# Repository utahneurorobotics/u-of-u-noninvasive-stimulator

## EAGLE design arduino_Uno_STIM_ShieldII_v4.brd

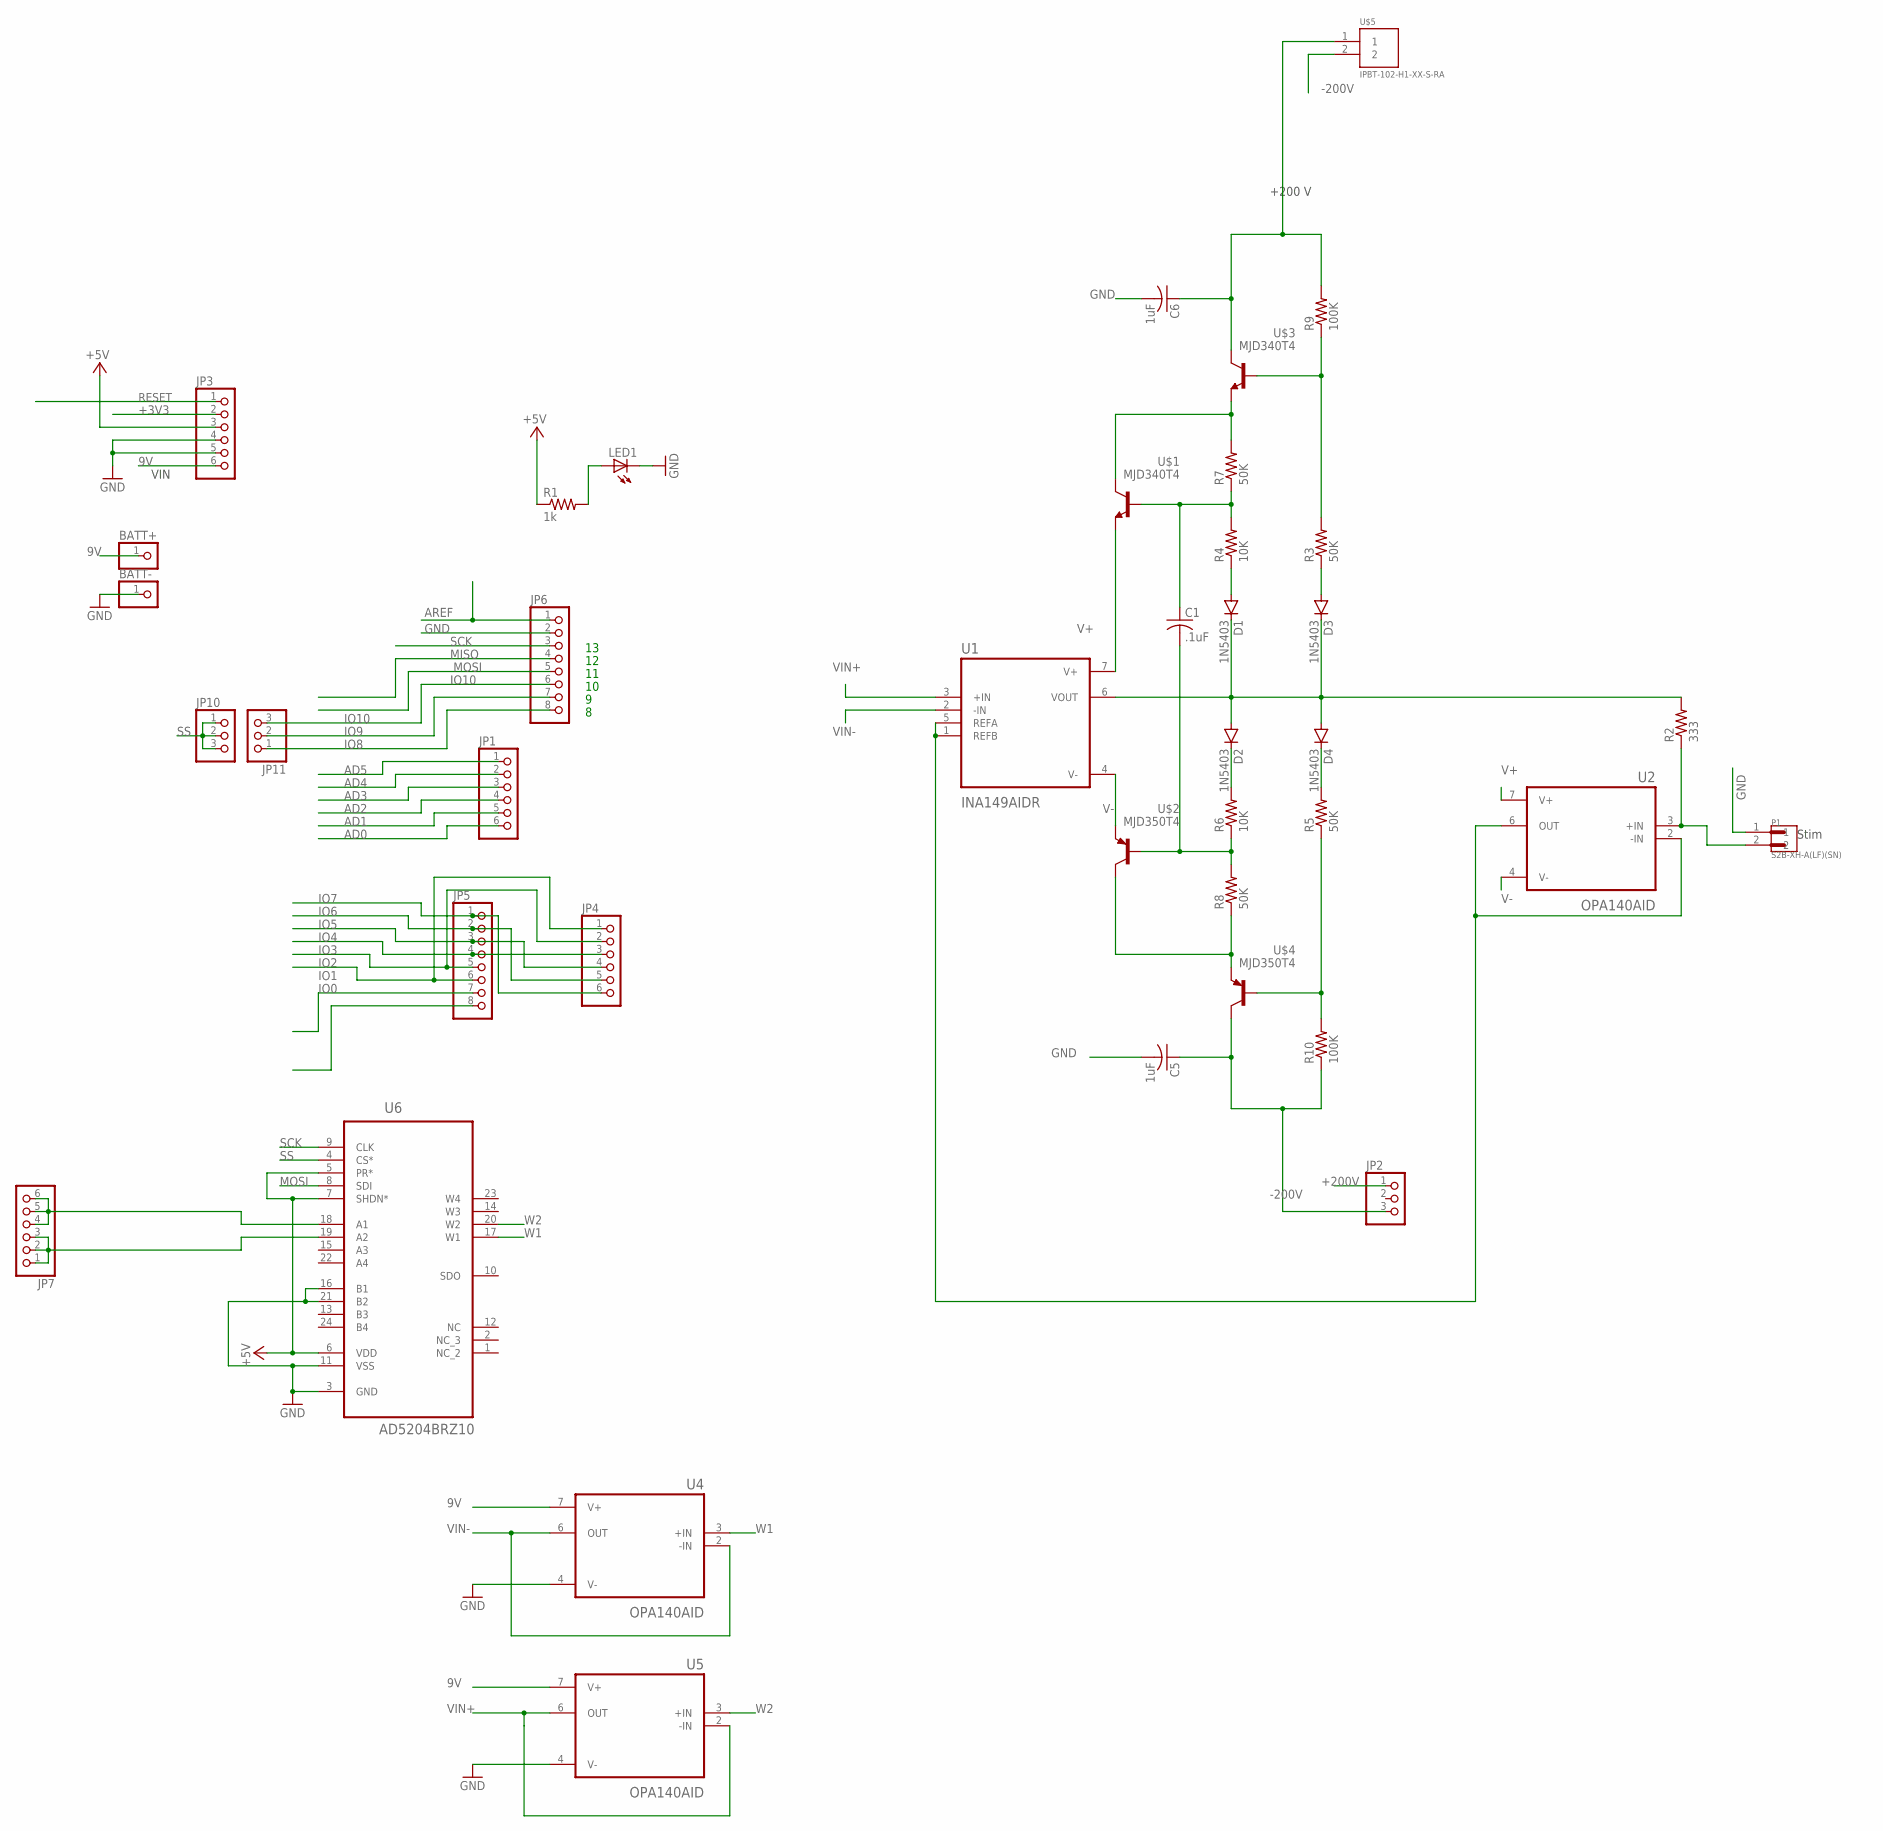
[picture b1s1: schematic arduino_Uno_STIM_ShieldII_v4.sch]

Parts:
BATT+: PINHD-1X1; 1X01
BATT-: PINHD-1X1; 1X01
C1: .1uF; C1206
C5, C6: 1uF; C2220K
D1, D2, D3, D4: 1N5403; DO201-15
JP1, JP3, JP4, JP7: PINHD-1X6CB; 1X06-CLEANBIG
JP2: PINHD-1X3; 1X03
JP5, JP6: PINHD-1X8CLEANBIG; 1X08-CLEANBIG
JP10, JP11: PINHD-1X3CB; 1X03-CLEANBIG
LED1: LEDCHIPLED_1206; CHIPLED_1206
P1: S2B-XH-A(LF)(SN); JST_S2B-XH-A(LF)(SN)
R1: 1k; M0805
R2: 333; M1206
R3, R5, R7, R8: 50K; M1206
R4, R6: 10K; M1206
R9, R10: 100K; M1206
U1: INA149AIDR; SOIC127P599X175-8N
U2, U4, U5: OPA140AID; SOIC127P599X175-8N
U6: AD5204BRZ10; SOIC127P1032X265-24N
U$1, U$3: MJD340T4; TO229P990X238-4N
U$2, U$4: MJD350T4; TO229P990X238-4N
U$5: IPBT-102-H1-XX-S-RA

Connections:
9V: BATT+.1, JP3.6, U4.7 (V+), U5.7 (V+)
+3V3: JP3.2
+5V: JP3.3, R1.1, U6.5 (PR*), U6.6 (VDD), U6.7 (SHDN*)
+200V: C6.1, JP2.1, R9.2, U$3.4 (C), U$5.1
-200V: C5.1, JP2.3, R10.1, U$4.4 (C), U$5.2
AD0: JP1.6
AD1: JP1.5
AD2: JP1.4
AD3: JP1.3
AD4: JP1.2
AD5: JP1.1
AREF: JP6.1
GND: BATT-.1, C5.2, C6.2, JP3.4, JP3.5, JP6.2, LED1.C, P1.1, U4.4 (V-), U5.4 (V-), U6.3 (GND), U6.11 (VSS), U6.16 (B1), U6.21 (B2)
IO0: JP5.8
IO1: JP5.7
IO2: JP4.1, JP5.6
IO3: JP4.2, JP5.5
IO4: JP4.3, JP5.4
IO5: JP4.4, JP5.3
IO6: JP4.5, JP5.2
IO7: JP4.6, JP5.1
IO8: JP6.8, JP11.1
IO9: JP6.7, JP11.2
IO10: JP6.6, JP11.3
MISO: JP6.4
MOSI: JP6.5, U6.8 (SDI)
unnamed: D1.C, D2.A, D3.C, D4.A, R2.2, U1.6 (VOUT)
unnamed: D3.A, R3.1
unnamed: LED1.A, R1.2
unnamed: JP7.4, JP7.5, JP7.6, U6.18 (A1)
unnamed: JP7.1, JP7.2, JP7.3, U6.19 (A2)
unnamed: D1.A, R4.1
unnamed: P1.2, R2.1, U2.3 (+IN)
unnamed: D4.C, R5.2
unnamed: D2.C, R6.2
unnamed: C1.2, R6.1, R8.2, U$2.1 (B)
unnamed: C1.1, R4.2, R7.1, U$1.1 (B)
unnamed: R7.2, U$1.4 (C), U$3.3 (E)
unnamed: R8.1, U$2.4 (C), U$4.3 (E)
unnamed: R3.2, R9.1, U$3.1 (B)
unnamed: R5.1, R10.2, U$4.1 (B)
unnamed: U1.1 (REFB), U1.5 (REFA), U2.2 (-IN), U2.6 (OUT)
RESET: JP3.1
SCK: JP6.3, U6.9 (CLK)
SS: JP10.1, JP10.2, JP10.3, U6.4 (CS*)
V+: U1.7 (V+), U2.7 (V+), U$1.3 (E)
V-: U1.4 (V-), U2.4 (V-), U$2.3 (E)
VIN+: U1.3 (+IN), U5.2 (-IN), U5.6 (OUT)
VIN-: U1.2 (-IN), U4.2 (-IN), U4.6 (OUT)
W1: U4.3 (+IN), U6.17 (W1)
W2: U5.3 (+IN), U6.20 (W2)

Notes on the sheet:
+200 V
Stim
VIN

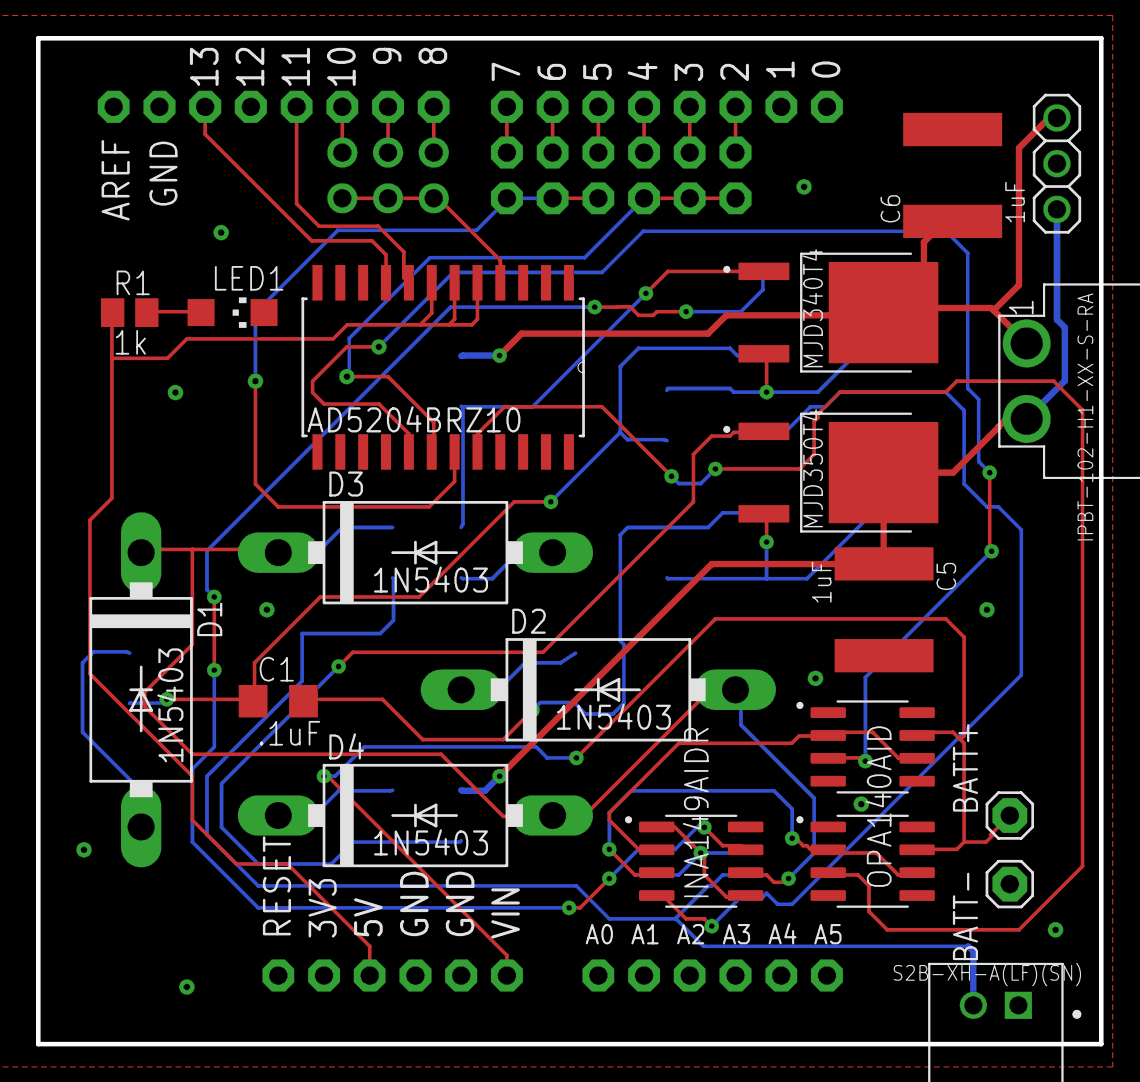
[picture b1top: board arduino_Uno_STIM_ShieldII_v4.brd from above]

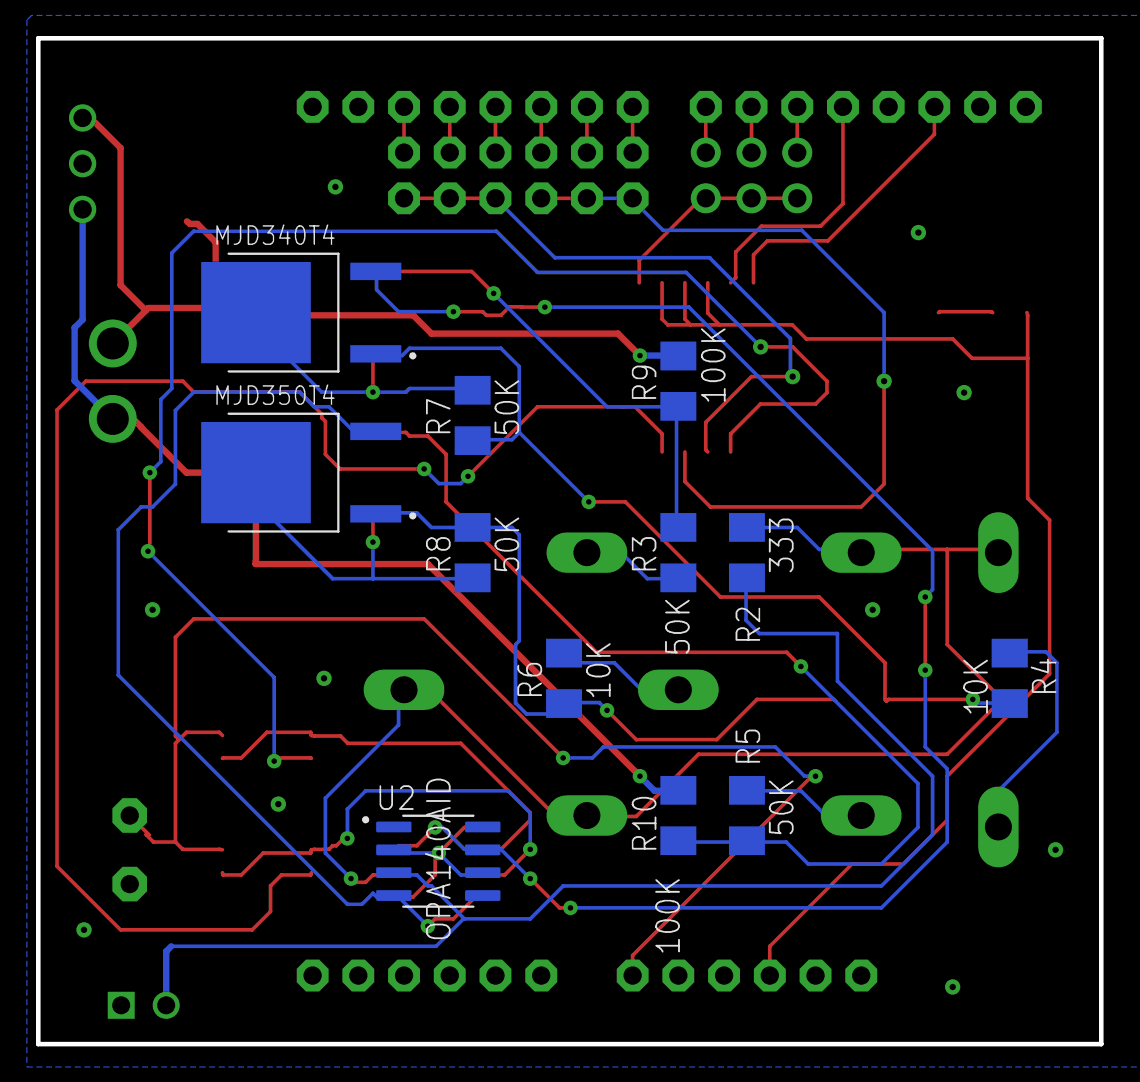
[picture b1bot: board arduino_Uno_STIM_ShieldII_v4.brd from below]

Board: 2 copper layers, 59.1 x 55.9 mm, 40 parts (12 on the bottom side), 39 nets.

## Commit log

2022-12-09 Add files via upload
    Added the EAGLE files
2023-11-18 Create README.txt for stimulator software
2023-11-18 Add files via upload
    Arduino software for controlling stimulator
2025-02-04 Update README.txt
    added ArdStim description
2025-02-04 Added ArdStim Matlab Class
2025-02-04 Delete Software/MultiChannel_StimShield_mat20231004/MultiChannel_StimShield_mat20231004.ino
    removed old version
2025-02-04 Added most recent stimulator code
